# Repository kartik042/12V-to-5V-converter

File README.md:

# 12V-to-5V-converter
A board that takes 12V DC input and steps it down to 5V DC with a switch to enable and disable output.

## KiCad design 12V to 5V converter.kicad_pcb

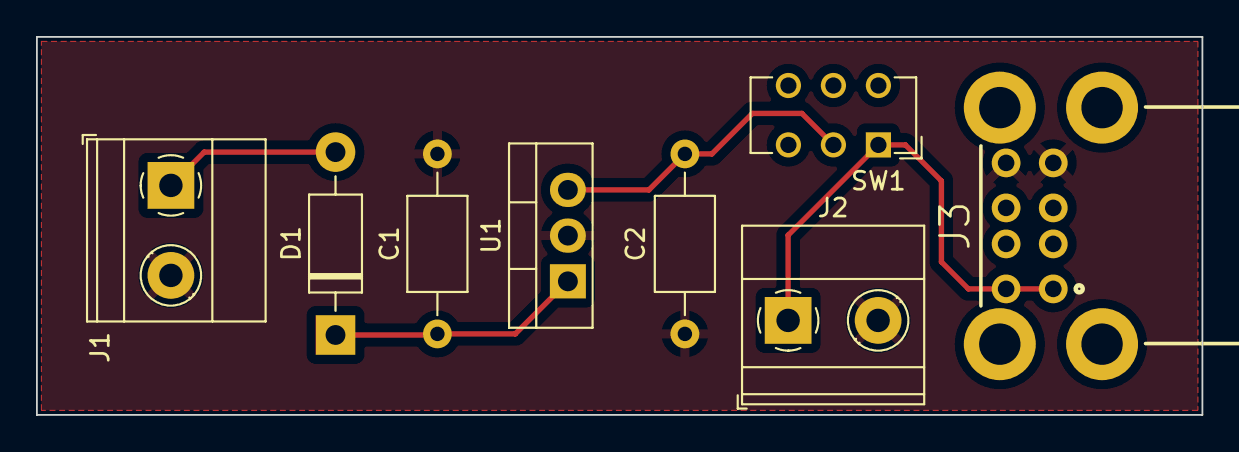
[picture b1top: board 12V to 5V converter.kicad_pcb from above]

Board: 2 copper layers, 64.8 x 21.0 mm, 8 parts (0 on the bottom side), 5 nets.

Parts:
C1: 470uF; C_Axial_L5.1mm_D3.1mm_P10.00mm_Horizontal
C2: 1uF; C_Axial_L5.1mm_D3.1mm_P10.00mm_Horizontal
D1: 1N4007; D_DO-41_SOD81_P10.16mm_Horizontal
J1, J2: Screw_Terminal_01x02; TerminalBlock_Phoenix_MKDS-1,5-2_1x02_P5.00mm_Horizontal
J3: USB1035-XX-X-X-X-B_REVE; GCT_USB1035-XX-X-X-X-B_REVE
SW1: SW_SPDT; SW_CuK_JS202011AQN_DPDT_Angled
U1: LM7805_TO220; TO-220-3_Vertical

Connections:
GND: C1.2, C2.2, J1.2, J2.2, J3.4A (GND1), J3.4B (GND2), U1.2 (GND)
unnamed: D1.2 (A), J1.1
unnamed: C1.1, D1.1 (K), U1.1 (VI)
unnamed: J2.1, J3.1A (VBUS1), J3.1B (VBUS2), SW1.1 (A)
unnamed: C2.1, SW1.2 (B), U1.3 (VO)

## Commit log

2025-04-25 Remove backup folder
2025-04-25 Add .gitignore
